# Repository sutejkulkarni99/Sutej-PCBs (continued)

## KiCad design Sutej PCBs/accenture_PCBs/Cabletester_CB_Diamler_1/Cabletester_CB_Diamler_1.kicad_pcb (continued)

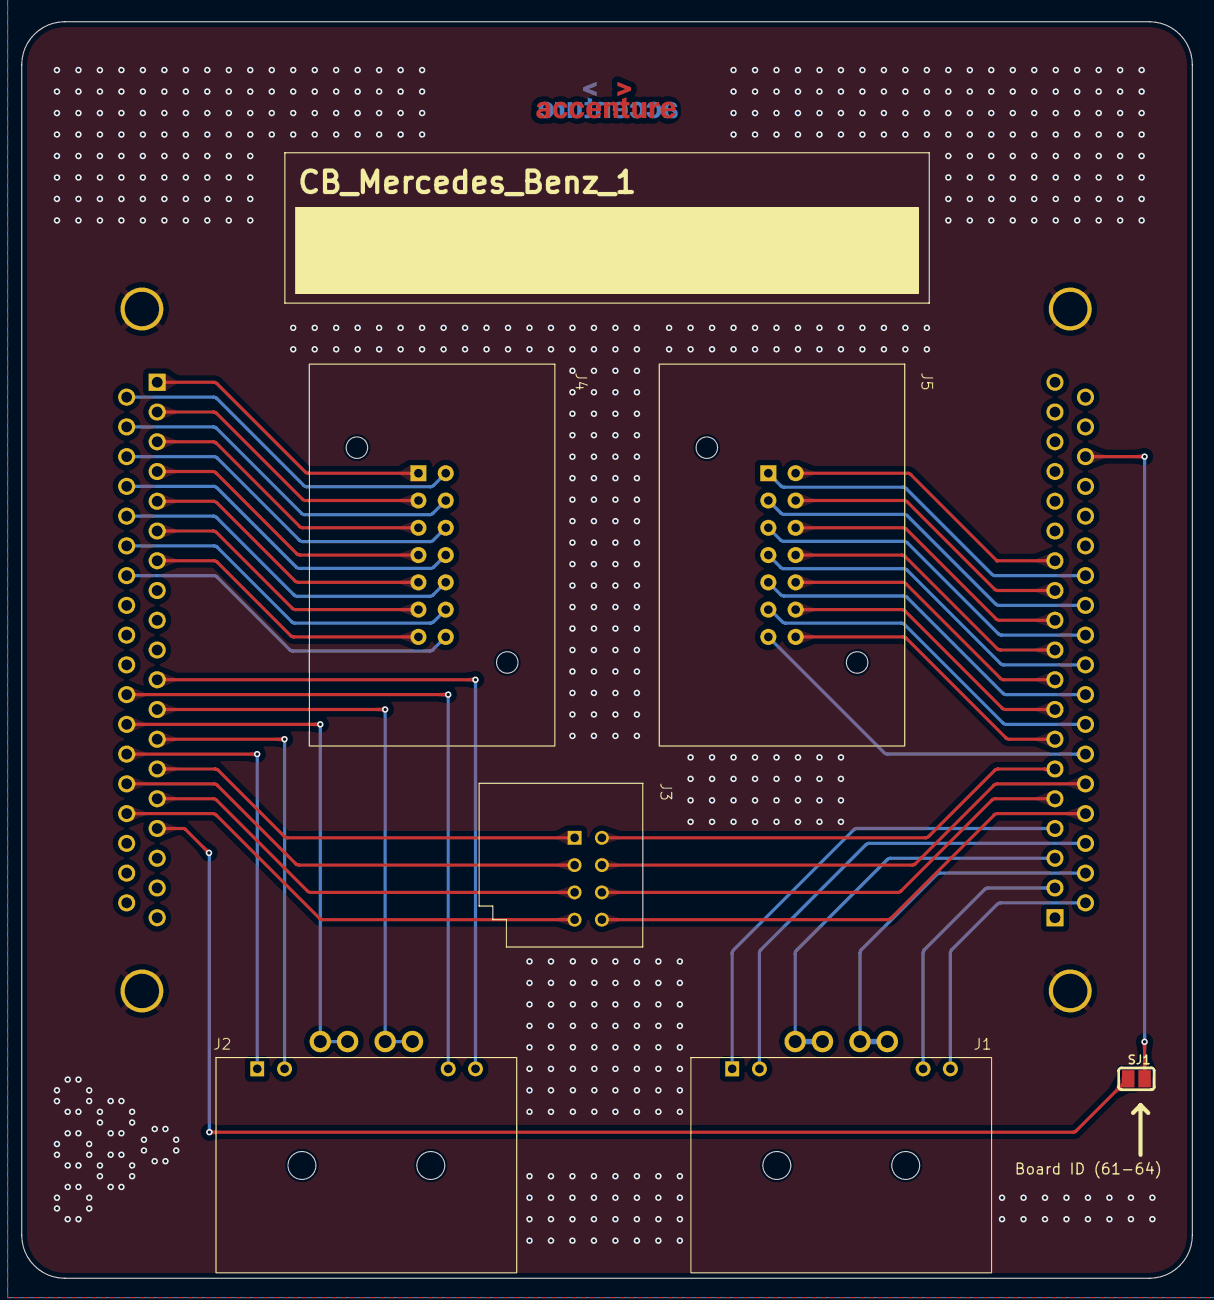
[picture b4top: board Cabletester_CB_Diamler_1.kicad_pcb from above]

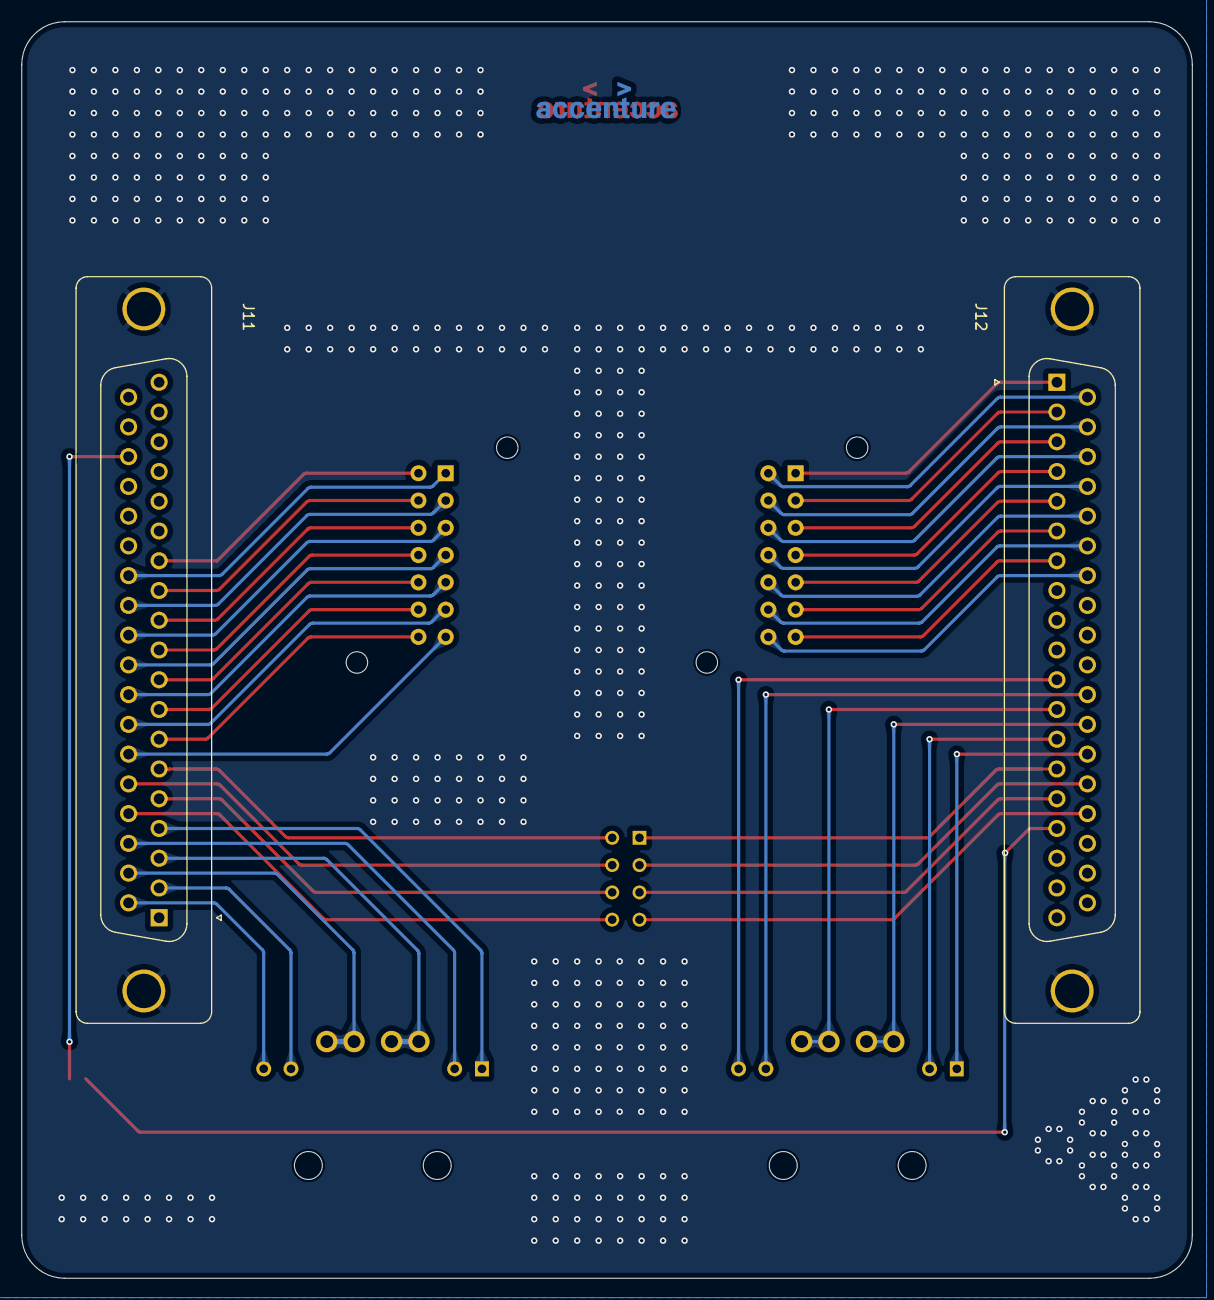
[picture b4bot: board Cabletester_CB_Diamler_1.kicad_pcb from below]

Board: 2 copper layers, 109.0 x 117.0 mm, 10 parts (3 on the bottom side), 51 nets.

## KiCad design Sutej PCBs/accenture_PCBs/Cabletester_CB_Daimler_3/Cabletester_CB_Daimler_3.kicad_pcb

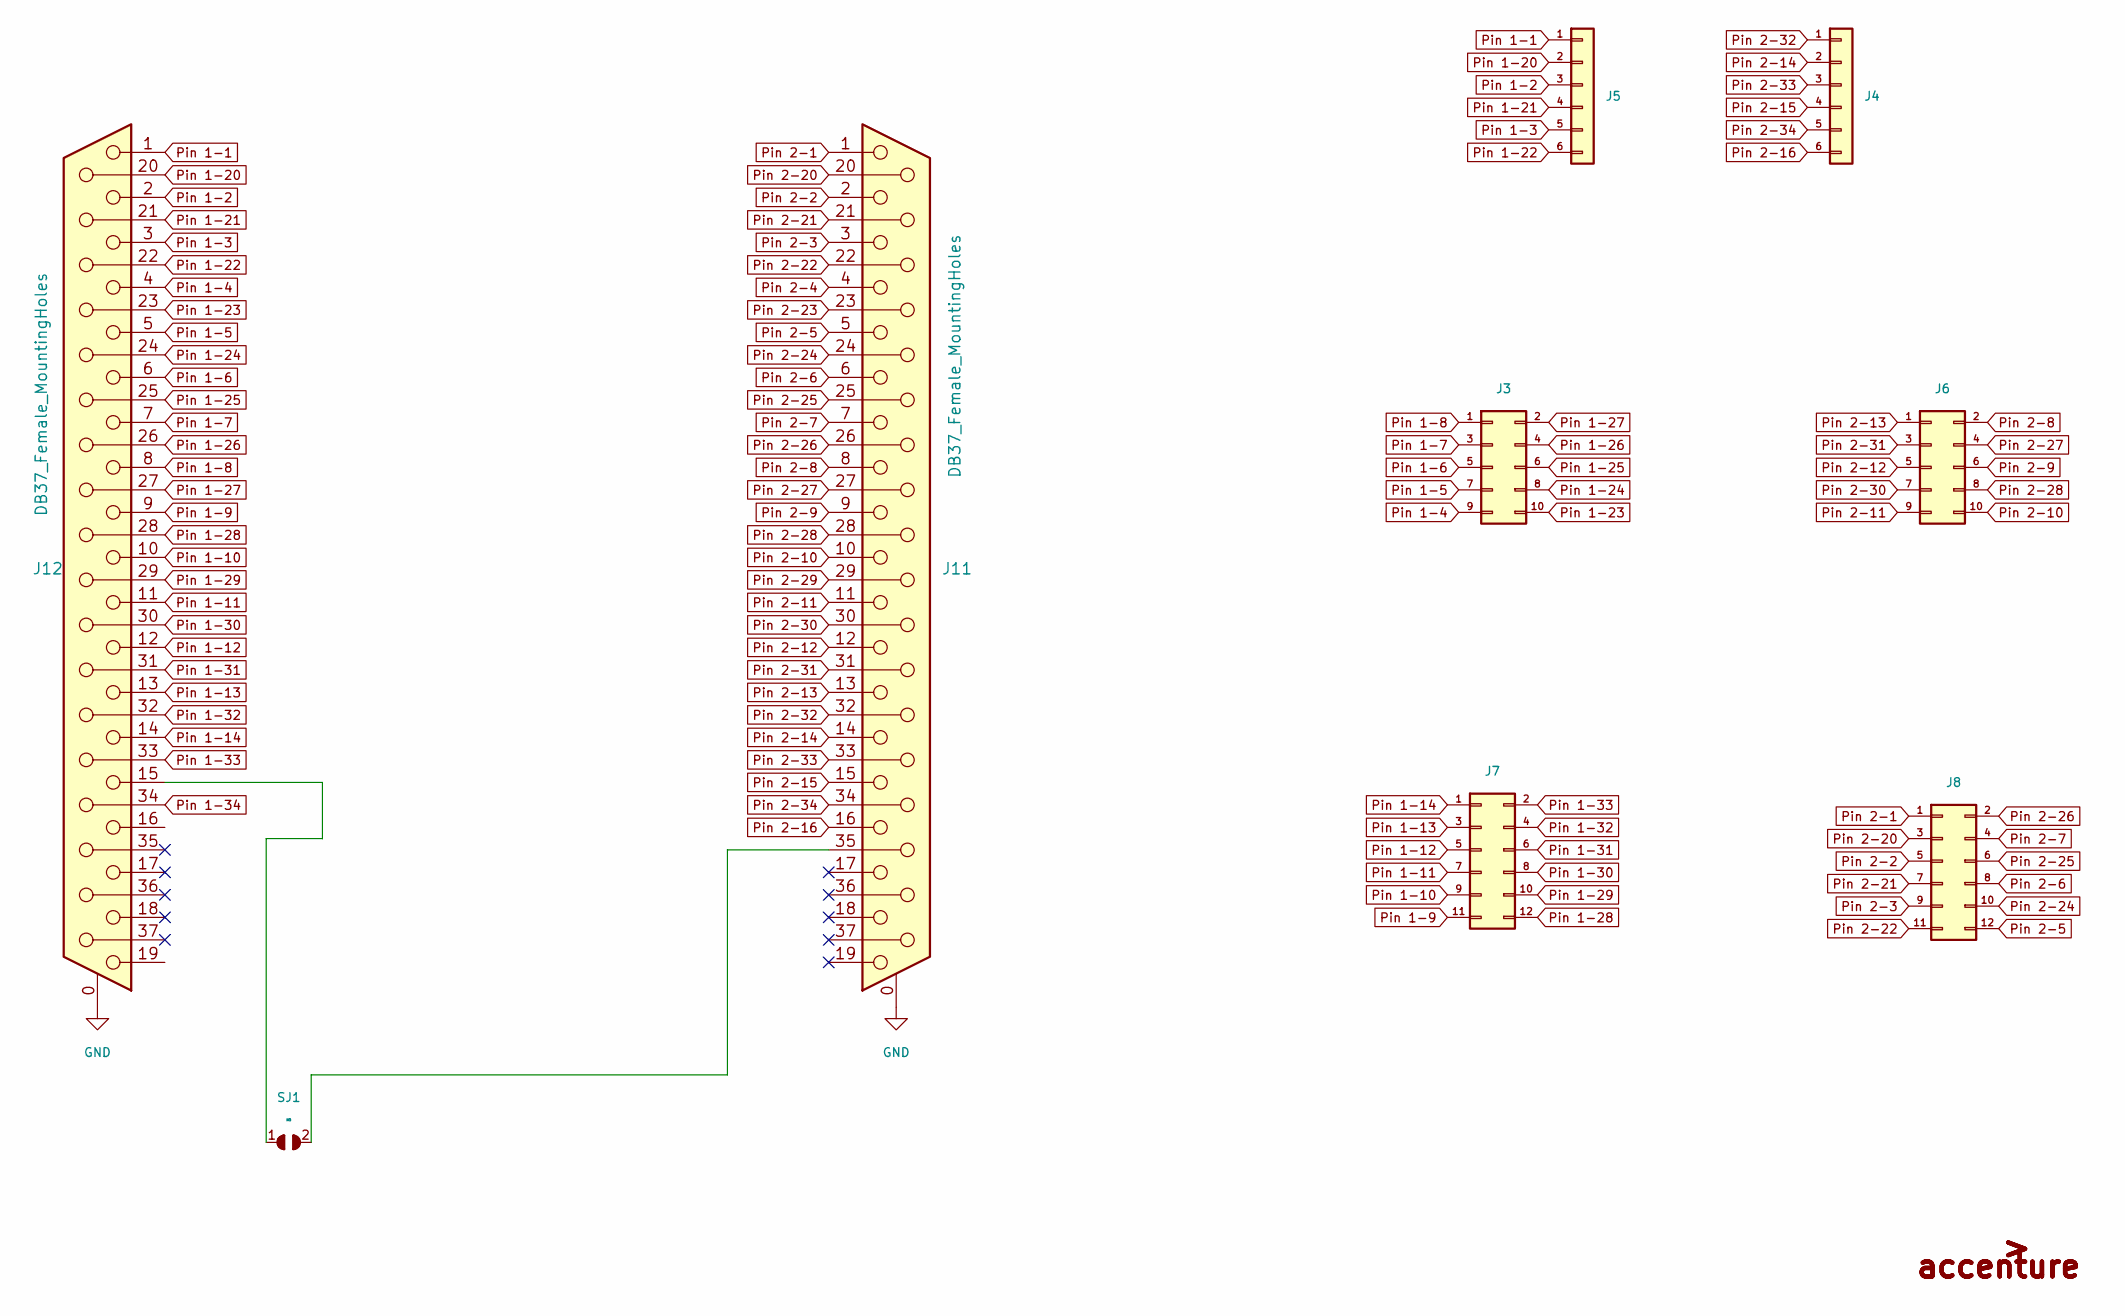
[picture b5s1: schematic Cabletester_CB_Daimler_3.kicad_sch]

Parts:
J3, J6: Conn_02x05_2.54mm_straight; WR-PHD_61301021121_05x2.54mm_Straight; Farnell 1841232
J4, J5: Conn_01x06_Male; Molex_KK254_022032061_01_06x2.54mm_Straight; Farnell 9731113
J7, J8: Conn_02x05_2.54mm_straight; PIN-HEADER-2.54MM-2X06; Farnell 1841232
J11, J12: DB37_Female_MountingHoles; DSUB-37_Female_Vertical_P2.77x2.84mm_MountingHoles; Farnell 2401248
Logo1, Logo2: Accenture-LOGO-13x3; Accenture-13x3
SJ1: SolderJumper-2pin; SJ

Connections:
GND: J11.0 (PAD), J12.0 (PAD)
unnamed: J11.35, SJ1.2
unnamed: J12.15, SJ1.1
Pin 1-1: J5.1, J12.1
Pin 1-2: J5.3, J12.2
Pin 1-3: J5.5, J12.3
Pin 1-4: J3.9, J12.4
Pin 1-5: J3.7, J12.5
Pin 1-6: J3.5, J12.6
Pin 1-7: J3.3, J12.7
Pin 1-8: J3.1, J12.8
Pin 1-9: J7.11, J12.9
Pin 1-10: J7.9, J12.10
Pin 1-11: J7.7, J12.11
Pin 1-12: J7.5, J12.12
Pin 1-13: J7.3, J12.13
Pin 1-14: J7.1, J12.14
Pin 1-20: J5.2, J12.20
Pin 1-21: J5.4, J12.21
Pin 1-22: J5.6, J12.22
Pin 1-23: J3.10, J12.23
Pin 1-24: J3.8, J12.24
Pin 1-25: J3.6, J12.25
Pin 1-26: J3.4, J12.26
Pin 1-27: J3.2, J12.27
Pin 1-28: J7.12, J12.28
Pin 1-29: J7.10, J12.29
Pin 1-30: J7.8, J12.30
Pin 1-31: J7.6, J12.31
Pin 1-32: J7.4, J12.32
Pin 1-33: J7.2, J12.33
Pin 1-34: J12.34
Pin 2-1: J8.1, J11.1
Pin 2-2: J8.5, J11.2
Pin 2-3: J8.9, J11.3
Pin 2-4: J11.4
Pin 2-5: J8.12, J11.5
Pin 2-6: J8.8, J11.6
Pin 2-7: J8.4, J11.7
Pin 2-8: J6.2, J11.8
Pin 2-9: J6.6, J11.9
Pin 2-10: J6.10, J11.10
Pin 2-11: J6.9, J11.11
Pin 2-12: J6.5, J11.12
Pin 2-13: J6.1, J11.13
Pin 2-14: J4.2, J11.14
Pin 2-15: J4.4, J11.15
Pin 2-16: J4.6, J11.16
Pin 2-20: J8.3, J11.20
Pin 2-21: J8.7, J11.21
Pin 2-22: J8.11, J11.22
Pin 2-23: J11.23
Pin 2-24: J8.10, J11.24
Pin 2-25: J8.6, J11.25
Pin 2-26: J8.2, J11.26
Pin 2-27: J6.4, J11.27
Pin 2-28: J6.8, J11.28
Pin 2-29: J11.29
Pin 2-30: J6.7, J11.30
Pin 2-31: J6.3, J11.31
Pin 2-32: J4.1, J11.32
Pin 2-33: J4.3, J11.33
Pin 2-34: J4.5, J11.34

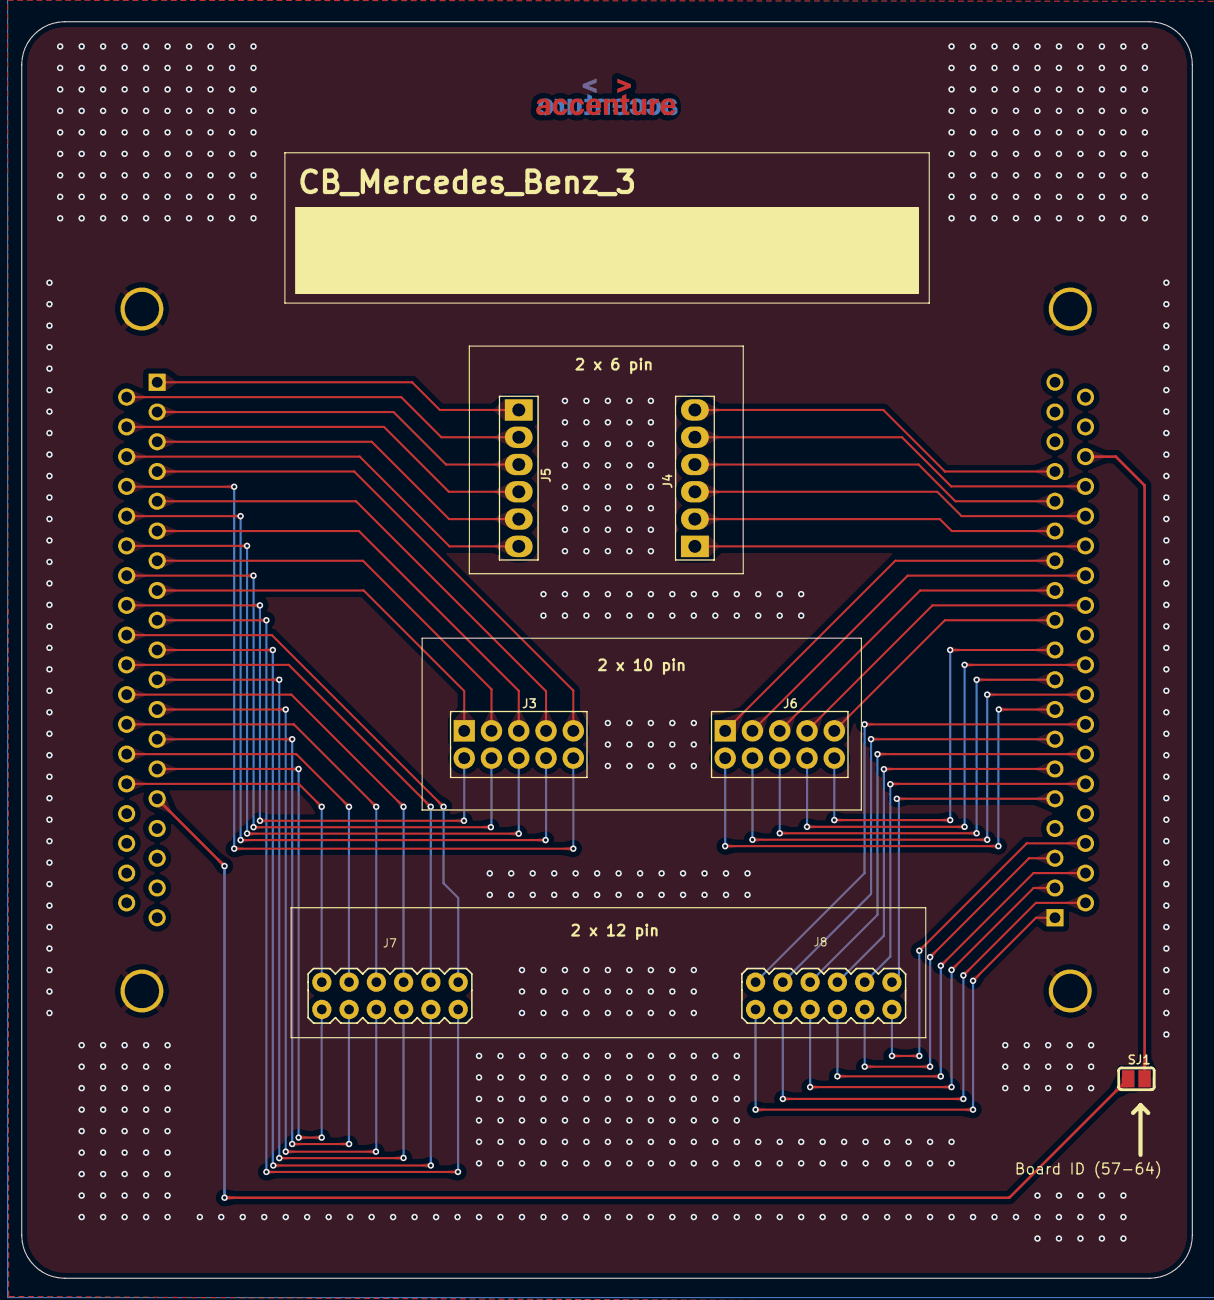
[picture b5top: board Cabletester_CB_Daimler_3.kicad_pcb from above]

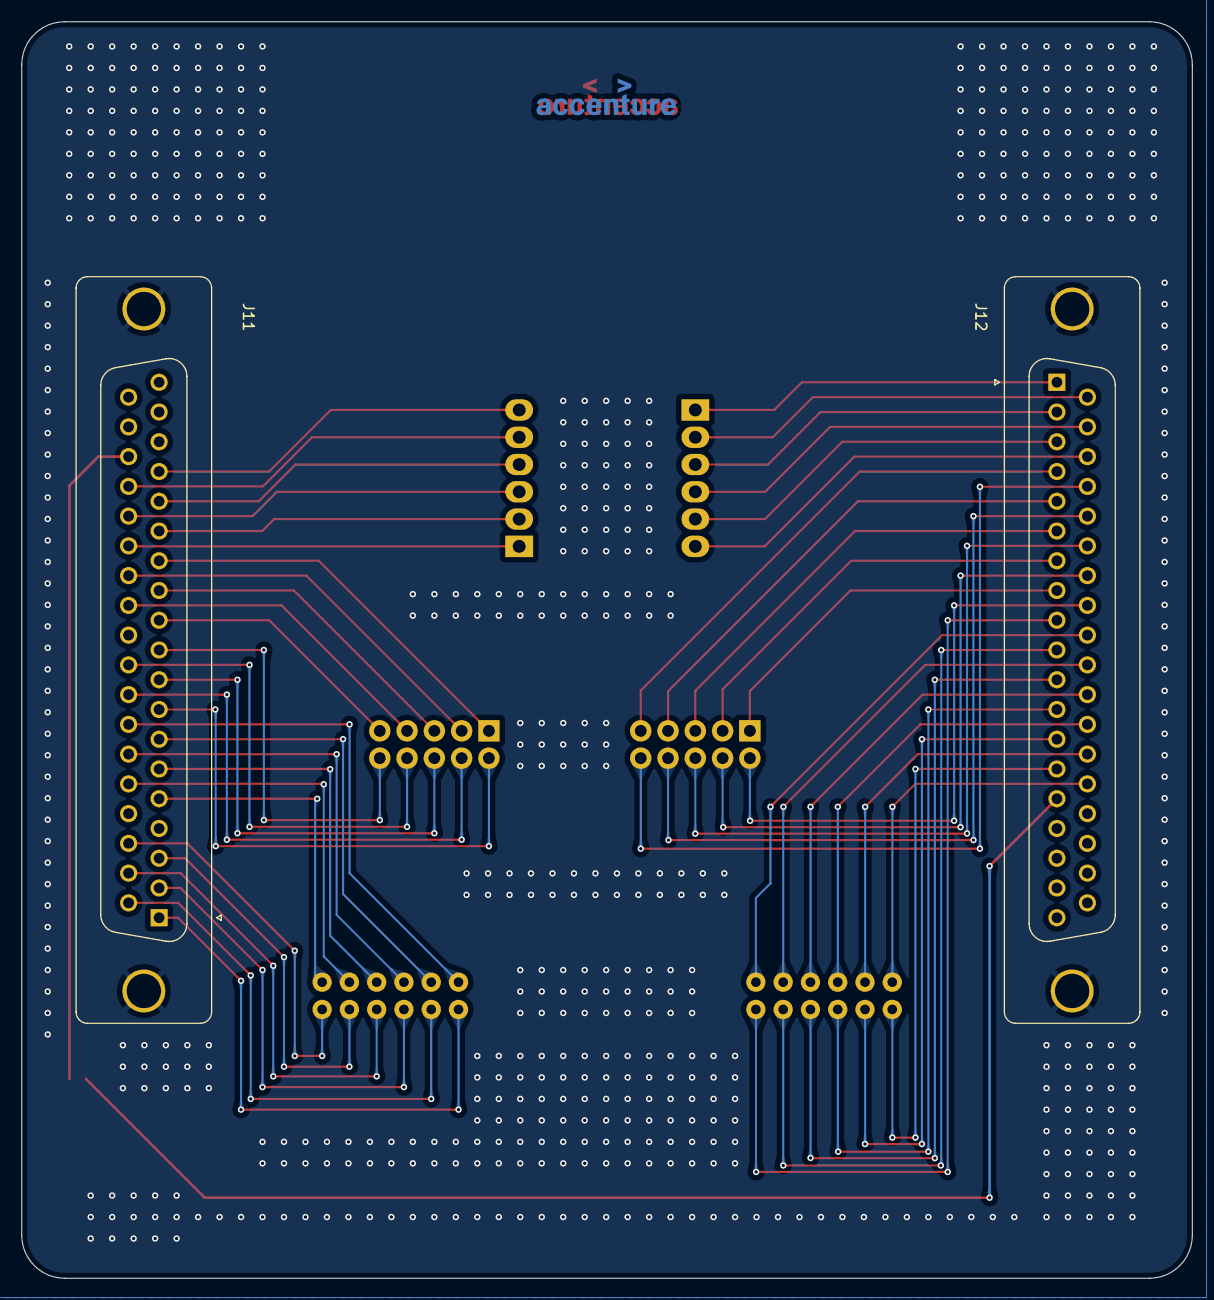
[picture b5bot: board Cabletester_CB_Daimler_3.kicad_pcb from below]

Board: 2 copper layers, 109.0 x 117.0 mm, 11 parts (3 on the bottom side), 59 nets.

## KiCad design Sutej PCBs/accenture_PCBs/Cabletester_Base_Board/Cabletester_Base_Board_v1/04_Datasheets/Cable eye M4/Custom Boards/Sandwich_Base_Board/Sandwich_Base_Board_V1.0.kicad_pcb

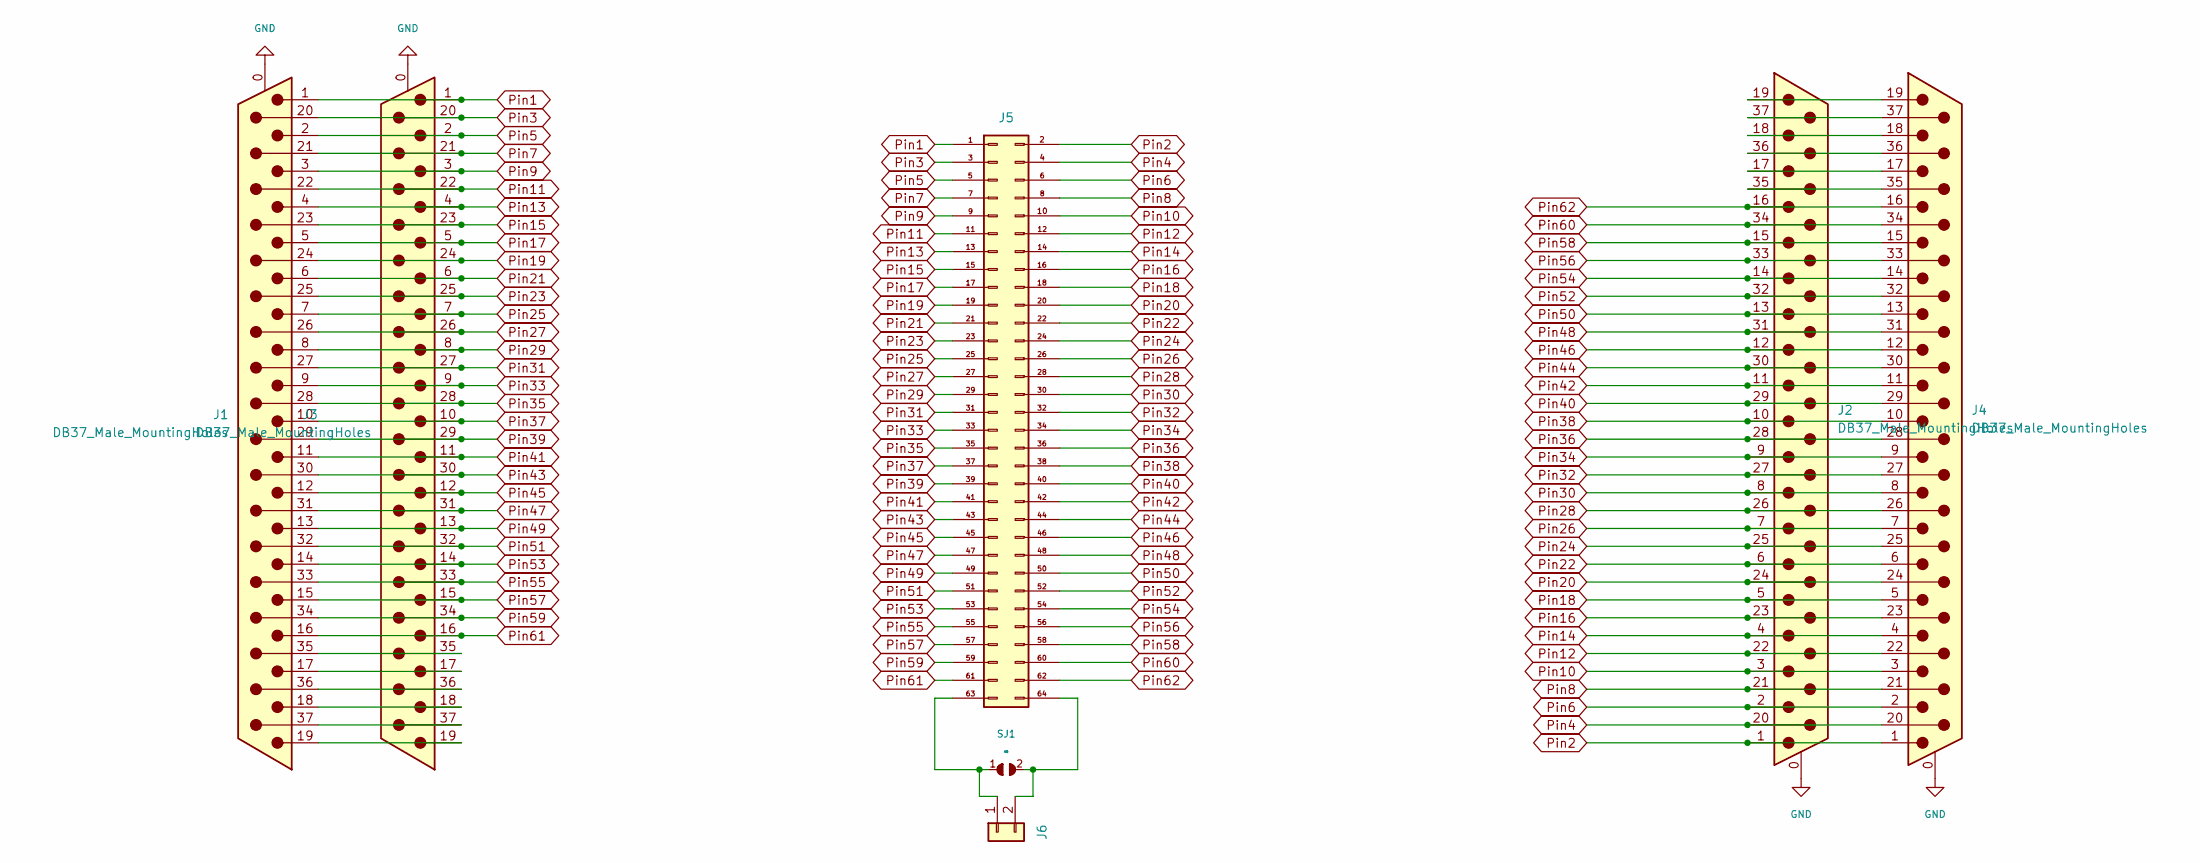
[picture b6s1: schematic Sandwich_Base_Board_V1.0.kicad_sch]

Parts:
J1, J2, J3, J4: DB37_Male_MountingHoles; DSUB-37_Male_Vertical_P2.77x2.84mm_MountingHoles
J5: Conn_02x32_2.54mm_Angeled; WR-PHD_61306421021_02x32_2.54mm_Angeled; Farnell 1841239
J6: Conn_01x02_2.54mm; WE-2-WR-TBL-2.54mm; Farnell 2356153
SJ1: SolderJumper-2pin; SJ

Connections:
GND: J1.0 (PAD), J2.0 (PAD), J3.0 (PAD), J4.0 (PAD)
unnamed: J1.17, J3.17
unnamed: J1.18, J3.18
unnamed: J1.19, J3.19
unnamed: J1.35, J3.35
unnamed: J1.36, J3.36
unnamed: J1.37, J3.37
unnamed: J2.17, J4.17
unnamed: J2.18, J4.18
unnamed: J2.19, J4.19
unnamed: J2.35, J4.35
unnamed: J2.36, J4.36
unnamed: J2.37, J4.37
unnamed: J5.63, J6.1, SJ1.1
unnamed: J5.64, J6.2, SJ1.2
Pin1: J1.1, J3.1, J5.1
Pin2: J2.1, J4.1, J5.2
Pin3: J1.20, J3.20, J5.3
Pin4: J2.20, J4.20, J5.4
Pin5: J1.2, J3.2, J5.5
Pin6: J2.2, J4.2, J5.6
Pin7: J1.21, J3.21, J5.7
Pin8: J2.21, J4.21, J5.8
Pin9: J1.3, J3.3, J5.9
Pin10: J2.3, J4.3, J5.10
Pin11: J1.22, J3.22, J5.11
Pin12: J2.22, J4.22, J5.12
Pin13: J1.4, J3.4, J5.13
Pin14: J2.4, J4.4, J5.14
Pin15: J1.23, J3.23, J5.15
Pin16: J2.23, J4.23, J5.16
Pin17: J1.5, J3.5, J5.17
Pin18: J2.5, J4.5, J5.18
Pin19: J1.24, J3.24, J5.19
Pin20: J2.24, J4.24, J5.20
Pin21: J1.6, J3.6, J5.21
Pin22: J2.6, J4.6, J5.22
Pin23: J1.25, J3.25, J5.23
Pin24: J2.25, J4.25, J5.24
Pin25: J1.7, J3.7, J5.25
Pin26: J2.7, J4.7, J5.26
Pin27: J1.26, J3.26, J5.27
Pin28: J2.26, J4.26, J5.28
Pin29: J1.8, J3.8, J5.29
Pin30: J2.8, J4.8, J5.30
Pin31: J1.27, J3.27, J5.31
Pin32: J2.27, J4.27, J5.32
Pin33: J1.9, J3.9, J5.33
Pin34: J2.9, J4.9, J5.34
Pin35: J1.28, J3.28, J5.35
Pin36: J2.28, J4.28, J5.36
Pin37: J1.10, J3.10, J5.37
Pin38: J2.10, J4.10, J5.38
Pin39: J1.29, J3.29, J5.39
Pin40: J2.29, J4.29, J5.40
Pin41: J1.11, J3.11, J5.41
Pin42: J2.11, J4.11, J5.42
Pin43: J1.30, J3.30, J5.43
Pin44: J2.30, J4.30, J5.44
Pin45: J1.12, J3.12, J5.45
Pin46: J2.12, J4.12, J5.46
Pin47: J1.31, J3.31, J5.47
Pin48: J2.31, J4.31, J5.48
Pin49: J1.13, J3.13, J5.49
Pin50: J2.13, J4.13, J5.50
Pin51: J1.32, J3.32, J5.51
Pin52: J2.32, J4.32, J5.52
Pin53: J1.14, J3.14, J5.53
Pin54: J2.14, J4.14, J5.54
Pin55: J1.33, J3.33, J5.55
Pin56: J2.33, J4.33, J5.56
Pin57: J1.15, J3.15, J5.57
Pin58: J2.15, J4.15, J5.58
Pin59: J1.34, J3.34, J5.59
Pin60: J2.34, J4.34, J5.60
Pin61: J1.16, J3.16, J5.61
Pin62: J2.16, J4.16, J5.62

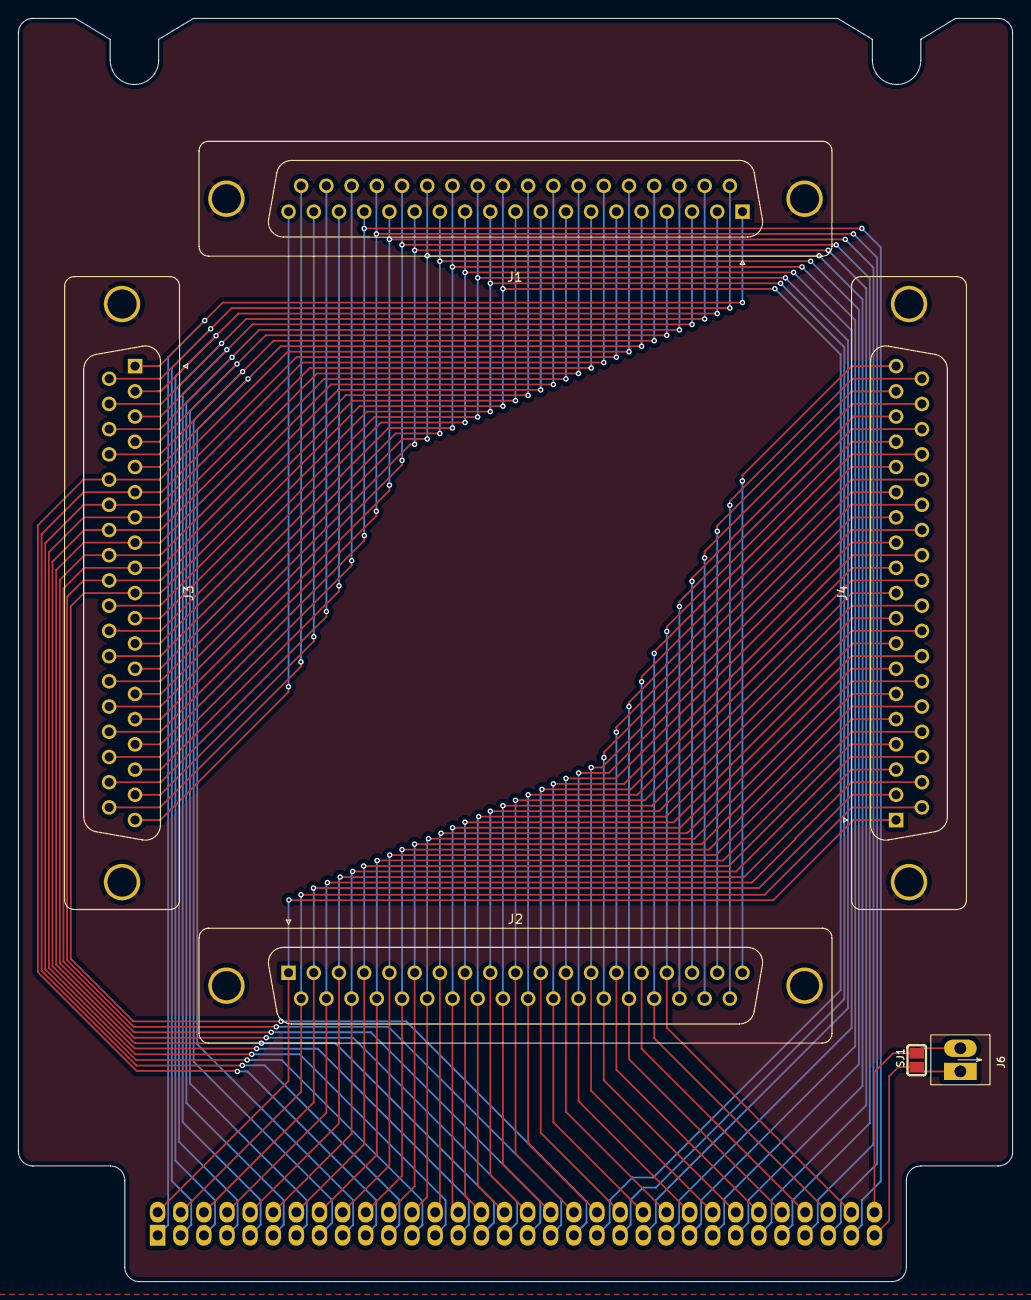
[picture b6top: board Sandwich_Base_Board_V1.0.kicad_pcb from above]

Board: 2 copper layers, 109.2 x 138.7 mm, 7 parts (1 on the bottom side), 77 nets.

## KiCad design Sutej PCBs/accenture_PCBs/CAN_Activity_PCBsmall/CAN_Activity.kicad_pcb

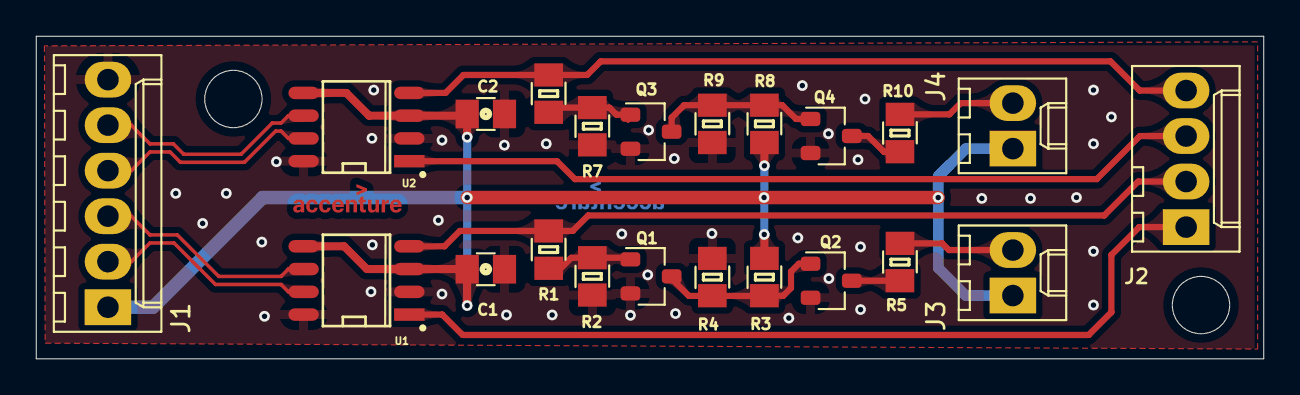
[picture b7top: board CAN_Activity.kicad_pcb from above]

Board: 2 copper layers, 68.5 x 18.0 mm, 24 parts (1 on the bottom side), 18 nets.

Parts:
C1, C2: 100nF50V_0805; C_0805_Big
J1: Conn_01x06_2.54mm_Molex22272061; Molex_KK-6410-06_06x2.54mm_Straight
J2: Conn_01x04_2.54mm_22112042; Molex_KK-6373-04_04x2.54mm_Straight
J3, J4: Conn_01x02_2.54mm_Molex_22-27-2021; Molex_KK-6410-02_02x2.54mm_Straight
Logo1, Logo2: Accenture-LOGO-7mm; Accenture-9x8
Q1, Q2, Q3, Q4: BSS123,215; SOT-23
R1, R3, R6, R8: 10k_0805; R_0805_Big
R2, R4, R7, R9: 22k_0805; R_0805_Big
R5, R10: 1k_0805; R_0805_Big
U1, U2: MCP2562FD-E_SN; SOIC-8-N

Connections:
+5V: C1.1, C2.1, J1.1 (5V), J3.1, J4.1, R3.2, R8.2, U1.3 (Vdd), U1.5 (Vio), U2.3 (Vdd), U2.5 (Vio)
CAN1_N: J1.3 (CAN1_L), U1.6 (CAN_L)
CAN1_P: J1.2 (GND), U1.7 (CAN_H)
CAN1_RXD: J2.2, R1.1, U1.4 (RXD)
CAN1_TXD: J2.1, U1.1 (TXD)
CAN2_N: J1.5 (CAN1_H), U2.6 (CAN_L)
CAN2_P: J1.4 (CAN2_L), U2.7 (CAN_H)
CAN2_RXD: J2.4, R6.1, U2.4 (RXD)
CAN2_TXD: J2.3, U2.1 (TXD)
GND: C1.2, C2.2, J1.6 (CAN2_H), Q1.2 (S), Q2.2 (S), Q3.2 (S), Q4.2 (S), R2.2, R4.2, R7.2, R9.2, U1.2 (Vss), U1.8 (StBy), U2.2 (Vss), U2.8 (StBy)
K_LED_CAN1: J3.2, R5.1
K_LED_CAN2: J4.2, R10.1
unnamed: Q1.3 (D), Q2.1 (G), R3.1, R4.1
unnamed: Q1.1 (G), R1.2, R2.1
unnamed: Q2.3 (D), R5.2
unnamed: Q3.3 (D), Q4.1 (G), R8.1, R9.1
unnamed: Q3.1 (G), R6.2, R7.1
unnamed: Q4.3 (D), R10.2

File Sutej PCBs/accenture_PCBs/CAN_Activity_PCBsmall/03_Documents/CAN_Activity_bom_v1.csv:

"Reference","Value","Datasheet","Footprint","Qty","APN","DigiKey","Distrelec","Farnell","Kemet","Microchip","Molex","Mouser","Nexperia","Panasonic","Price","RS","Vishay","WE","Web"
"C1,C2","100nF50V_0805","YES","Sebastian-Capacitors_SMD:C_0805_Big","2","C0036","","","1869054","C0805F104K5RACAUTO","","","80-C0805F104K5RAUTO","","","0,256","","","","https://www.mouser.de/ProductDetail/KEMET/C0805F104K5RACAUTO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"
"J1","Conn_01x06_2.54mm_Molex22272061","YES","Sebastian-Connectors_Molex:Molex_KK-6410-06_06x2.54mm_Straight","1","CON00106","","143-80-838","9731172","","","22272061","710-61300611121","","","0,288","176-9943","","61900611121","https://www.distrelec.de/de/kk-254-gerade-stecker-leiterplat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"
"J2","Conn_01x04_2.54mm_22112042","YES","Sebastian-Connectors_Molex:Molex_KK-6373-04_04x2.54mm_Straight","1","CON0058","","","1462955","","","22112042","538-22-11-2042","","","0,567","679-5527","","","https://www.mouser.de/ProductDetail/Molex/22-11-2042?qs=mrPi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"
"J3,J4","Conn_01x02_2.54mm_Molex_22-27-2021","YES","Sebastian-Connectors_Molex:Molex_KK-6410-02_02x2.54mm_Straight","2","CON00108","","","9731148","","","22-27-2021","538-22-27-2021","","","0,229","483-8461","","61300211121","https://www.mouser.de/ProductDetail/Molex/22-27-2021?qs=%2Fh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"
"Q1,Q2,Q3,Q4","BSS123,215","YES","Sebastian_TO_SOT_SMD:SOT-23","4","DIS00124","","","1510764","","","","771-BSS123-T/R","BSS123,215","","0,3","708-2419","","","https://www.mouser.de/ProductDetail/Nexperia/BSS123215?qs=me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"
"R1,R3,R6,R8","10k_0805","YES","Sebastian-Resistors_SMD:R_0805_Big","4","R0072","","","1750767","","","","667-ERJ-P06F1002V","","ERJ-P06F1002V","0,154","721-7820","","","https://www.mouser.de/ProductDetail/Panasonic/ERJ-P06F1002V?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"
"R2,R4,R7,R9","22k_0805","YES","Sebastian-Resistors_SMD:R_0805_Big","4","R000170","","","1652960","","","","71-CRCW0805J-22K-E3","","","0,085","812-3776","CRCW080522K0JNEA","","https://www.mouser.de/ProductDetail/Vishay-Dale/CRCW080522K0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"
"R5,R10","1k_0805","YES","Sebastian-Resistors_SMD:R_0805_Big","2","R0080","","","1738959","","","","71-CRCW08051K00FKEAH","","","0,2","812-3435","CRCW08051K00FKEAHP","","https://www.mouser.de/ProductDetail/Vishay-Dale/CRCW08051K00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"
"U1,U2","MCP2562FD-E_SN","YES","Sebastian_SMD_Packages:SOIC-8-N","2","IC0041","MCP2562FD-E/SN-ND","","2434899","","MCP2562FD-E/SN","","579-MCP2562FD-E/SN","","","1,18","165-2008","","","https://www.mouser.de/ProductDetail/Microchip-Technology/MCP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"
